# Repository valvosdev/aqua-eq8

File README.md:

# Aqua:eq8

> Open Hardware. Open Source. Smart Irrigation.

Aqua:eq8 is an open-source and open-hardware 8-zone smart irrigation controller designed for residential, commercial, greenhouse, and agricultural installations.

Built around the ESP32-C3-MINI-N4, Aqua:eq8 combines reliable irrigation control with secure connectivity, mobile management, OTA firmware updates, MQTT communication, and cloud integration while remaining fully self-hostable and hackable.

The project includes:

- ESP32 firmware
- Hardware schematics and PCB design
- Golang backend API
- React Native mobile application
- Docker, Kubernetes, and Helm deployment support

---

## Features

### Irrigation Control

- 8 independent irrigation zones
- Multiple zones can run simultaneously
- Configurable Master Valve support
- Configurable pump start delay
- Local manual operation without Internet
- Mobile application control
- MQTT-based communication
- Future scheduling support
- Future weather integration
- Emergency stop functionality

### Connectivity

- WiFi provisioning via BLE
- Bluetooth Low Energy onboarding
- MQTT communication
- OTA firmware updates
- Cloud synchronization
- Device telemetry

### Security

- ESP32 Secure Boot
- Flash Encryption
- Signed OTA updates
- TLS communication
- Device authentication
- Secure credential storage

### Reliability

- Offline-first operation
- Local control during Internet outages
- Hardware watchdog
- Software watchdog
- Automatic recovery
- Power-loss recovery

### Open Source

- Open firmware
- Open hardware
- Open API
- Open mobile app
- Self-hostable backend

---

# Repository Structure

```
aqua-eq8/
├── firmware/
│   ├── main/
│   ├── components/
│   ├── ble/
│   ├── wifi/
│   ├── mqtt/
│   ├── ota/
│   └── valve/
│
├── hardware/
│   ├── schematic/
│   ├── pcb/
│   ├── enclosure/
│   └── bom/
│
├── api/
│   ├── cmd/
│   ├── internal/
│   ├── deployments/
│   ├── helm/
│   └── docker/
│
├── mobile/
│   ├── src/
│   ├── ios/
│   └── android/
│
└── docs/

```

# Hardware

## Power

The controller is powered by a standard irrigation transformer.

### Input

text 24VAC Barrel Jack 

### Internal Rails

```
text 24VAC  ├── Valve Outputs  ├── Current Monitoring  └── AC/DC Converter       ├── 5V       └── 3.3V 
```
---

## Main Components

### MCU

- ESP32-C3-MINI-N4
- WiFi 2.4GHz
- Bluetooth Low Energy
- 4MB Flash

### Output Expansion

Two 74HC595 shift registers are used:

#### Shift Register #1

Controls:

- 8 TRIAC outputs
- 8 Green status LEDs

#### Shift Register #2

Controls:

- 8 Red Master LEDs

This minimizes GPIO usage while allowing future expansion.

### Valve Drivers

- TRIAC-based switching
- Designed for 24VAC sprinkler valves
- RC snubber protection per channel
- Future current sensing support

### Protection

- Input fuse
- Snubber protection on every channel
- Brownout protection
- Hardware watchdog
- Secure boot
- Flash encryption

---

# Channel Controls

## Channels 1-8

Each button controls one irrigation zone.

### Short Press

Toggle zone state.

| Current State | Action |
|--------------|----------|
| OFF | Turn ON |
| ON | Turn OFF |

### Long Press

Toggle Master Valve assignment.

| Current State | Action |
|--------------|----------|
| Normal Zone | Set as Master |
| Master Zone | Remove Master |

Only one channel may be configured as Master at a time.

---

# Master Valve Operation

A Master Valve is commonly used for:

- Main water supply
- Pump control
- Pressure system enable

When any non-master zone is enabled:

1. Master Valve turns ON immediately
2. Zone enters waiting state
3. Configurable delay timer starts
4. Zone activates after delay

Example:

text Channel 1 = Master  User enables Channel 3  Channel 1 ON immediately  Channel 3 LED flashes  5 second delay  Channel 3 ON 

When the last active zone stops:

text Channel 3 OFF  No active zones remaining  Channel 1 OFF 

### Default Delay

yaml master_delay_seconds: 5 

Configurable through the mobile application.

---

# Channel LED Behavior

Each channel button contains:

- Green LED
- Red LED

## Green LED

Indicates operational state.

| State | Green |
|---------|---------|
| OFF | OFF |
| Waiting Master Delay | Flashing |
| Active | Solid |

## Red LED

Indicates configuration state.

| State | Red |
|---------|---------|
| Normal Zone | OFF |
| Master Zone | Solid |

## Combined States

| State | Green | Red |
|---------|---------|---------|
| OFF | OFF | OFF |
| ON | ON | OFF |
| Master OFF | OFF | ON |
| Master ON | ON | ON |
| Waiting Delay | Flashing | OFF |

---

# Status Button (Button 9)

Button 9 is a dedicated RGB status and management button.

Functions:

- Device Status
- BLE Pairing
- Factory Reset

---

## RGB Status LED

The status LED always displays the highest priority state.

Priority:

text Error OTA Update BLE Connected BLE Advertising WiFi Connected Booting 

### States

| State | RGB |
|---------|---------|
| Booting | White Breathing |
| WiFi Connected | Solid Green |
| BLE Advertising | Blue Breathing |
| Mobile App Connected | Solid Blue |
| OTA Update | Purple Breathing |
| Error | Red Flashing |

---

## Button Actions

### Short Press

Enable BLE pairing mode.

LED:

text Blue Breathing 

Duration:

text 10 Minutes 

### Long Press (10 Seconds)

Factory Reset.

Deletes:

- WiFi Credentials
- MQTT Configuration
- Device Pairing
- Local Configuration
- Schedules

LED:

text Red Breathing 

Device automatically reboots.

---

# Connectivity

Aqua:eq8 intentionally avoids:

- Captive Portals
- Access Point Setup
- Embedded Web UI

All device provisioning is performed through Bluetooth Low Energy.

### Provisioning Flow

text Power Device       ↓ Press Status Button       ↓ BLE Pairing       ↓ Mobile App       ↓ Send WiFi Credentials       ↓ Connect to Network       ↓ Register with Backend       ↓ MQTT Connected 

---

# MQTT

MQTT is the primary communication mechanism between the controller and backend services.

## Topics

text aquaeq8/{deviceId}/state aquaeq8/{deviceId}/events aquaeq8/{deviceId}/telemetry aquaeq8/{deviceId}/command aquaeq8/{deviceId}/ota 

## Example Telemetry

json {   "uptime": 86400,   "wifi_rssi": -62,   "free_heap": 124832,   "active_zones": [2,4,7] } 

MQTT data can be consumed directly by:

- Telegraf
- InfluxDB
- TimescaleDB
- VictoriaMetrics
- Grafana

---

# Firmware

Location:

text /firmware 

Built using:

- ESP-IDF
- FreeRTOS
- C/C++

## Features

### Device Control

- Zone management
- Master Valve logic
- Delay handling
- Local operation

### Connectivity

- BLE provisioning
- WiFi management
- MQTT client

### OTA

- Signed firmware updates
- Rollback protection
- Secure update process

### Security

- Secure Boot
- Flash Encryption
- Device authentication

### Reliability

- Hardware watchdog
- Software watchdog
- Crash recovery

---

# Backend API

Location:

text /api 

Built using:

- Go 1.26+
- PostgreSQL
- Redis
- MQTT

## Features

### Device Management

- Device registration
- Pairing
- Configuration synchronization

### Monitoring

- Online/offline status
- Telemetry collection
- Device diagnostics

### Security

- JWT authentication
- TLS communication
- API rate limiting

---

# Deployment

## Docker

bash docker compose up -d 

## Kubernetes

bash kubectl apply -f deployments/ 

## Helm

bash helm install aquaeq8 ./helm 

---

# Mobile Application

Location:

text /mobile 

Built using:

- React Native
- TypeScript

## Features

### Device Setup

- BLE discovery
- WiFi provisioning
- Device pairing

### Device Management

- Zone control
- Master Valve configuration
- Delay configuration

### Monitoring

- Device health
- Connectivity status
- Telemetry visualization

### OTA

- Firmware update notifications
- Update progress monitoring

---

# Future Features

## Planned

- Irrigation schedules
- Weather integration
- Rain delay
- Seasonal adjustments
- Water usage analytics

## Hardware Expansion

- Flow meter support
- Rain sensor input
- Valve current monitoring
- Leak detection
- Pump monitoring

---

# Valve Current Monitoring

Future versions may include electrical current sensing on each output channel.

Benefits:

- Detect disconnected valves
- Detect broken wires
- Detect short circuits
- Detect stuck valves
- Improve diagnostics

Example:

text Zone 4 ON  Expected Current: 220mA Measured Current: 0mA  Alert: Valve Not Connected 

---

# Development

## [Firmware](firmware)

bash cd firmware  idf.py build idf.py flash idf.py monitor 

## [Backend](api)

bash cd api  go run ./cmd/server 

## [Mobile](mobile)

bash cd mobile  yarn install

bash cd mobile  yarn install yarn start 

---

# Security Model

Every controller includes:

- Unique Device ID
- Device Certificate
- Private Key

Firmware security:

- Secure Boot enabled
- Flash Encryption enabled
- Signed OTA updates only

The controller never accepts unsigned firmware images.

---

# Contributing

Contributions are welcome.

Areas where help is needed:

- Embedded development
- Hardware design
- Backend development
- Mobile development
- Testing
- Documentation

Please open an issue or submit a pull request.

---

# License

MIT License

See [LICENSE](LICENSE) for details.

---

# Philosophy

Aqua:eq8 is built around three principles.

## Open Source

All software is publicly available.

## Open Hardware

PCB layouts and schematics are publicly available.

## Local First

Your irrigation system continues operating even if the Internet does not.

---

Aqua:eq8

An open-source, secure, MQTT-native irrigation controller built for modern gardens, farms, and greenhouses.

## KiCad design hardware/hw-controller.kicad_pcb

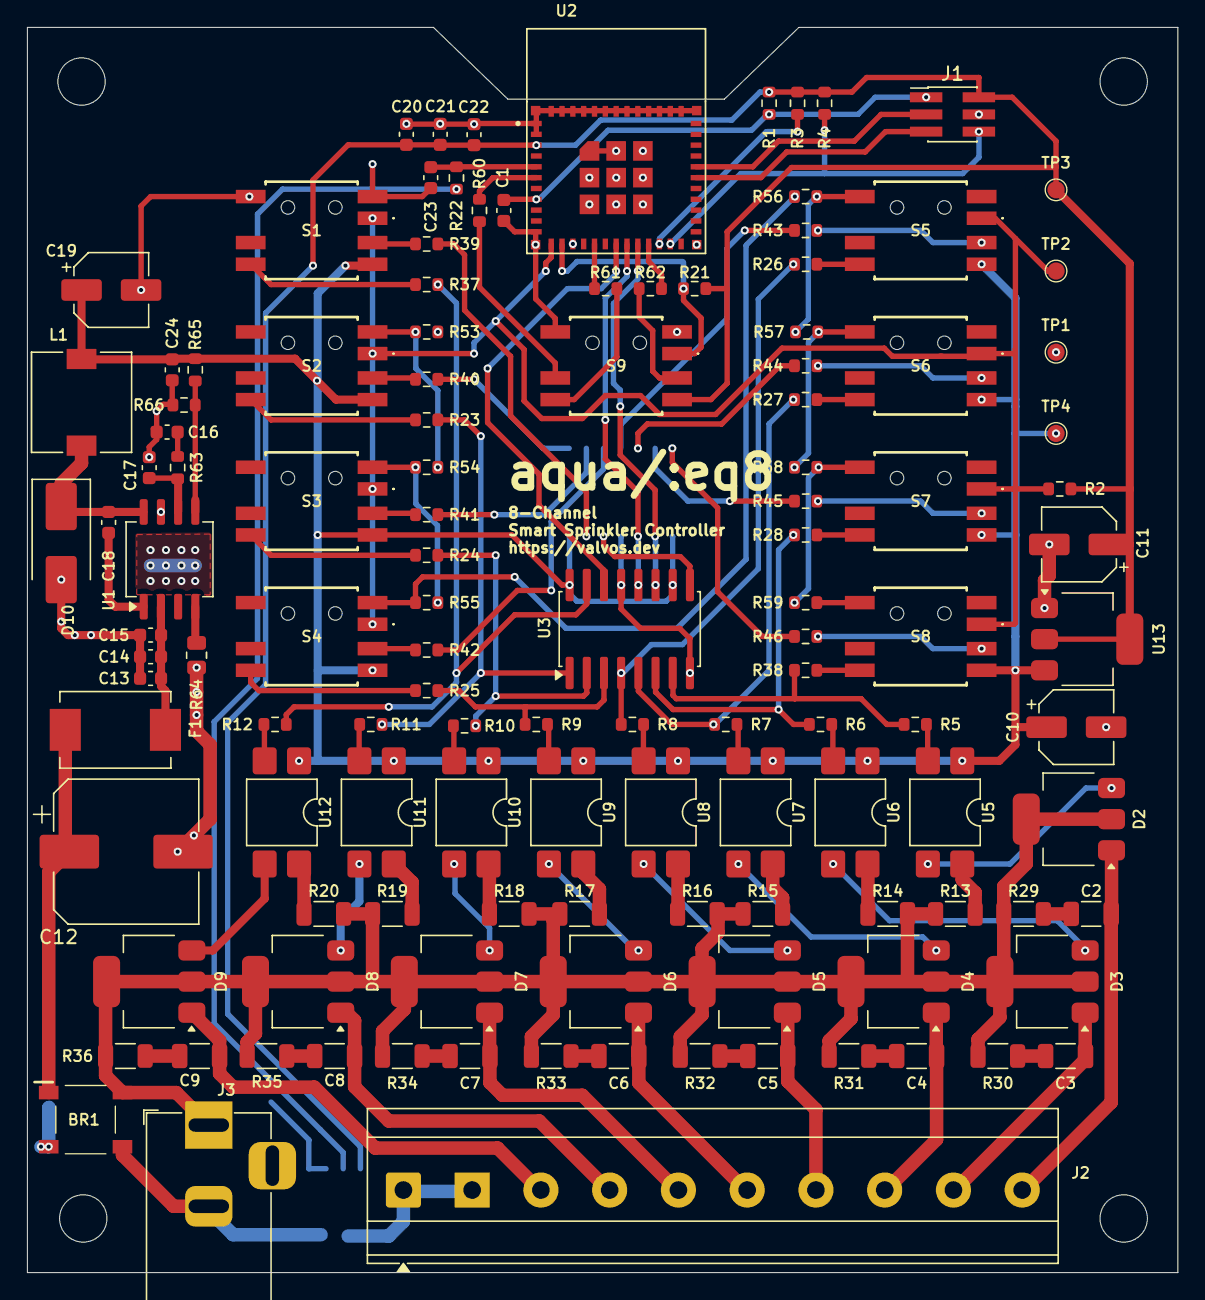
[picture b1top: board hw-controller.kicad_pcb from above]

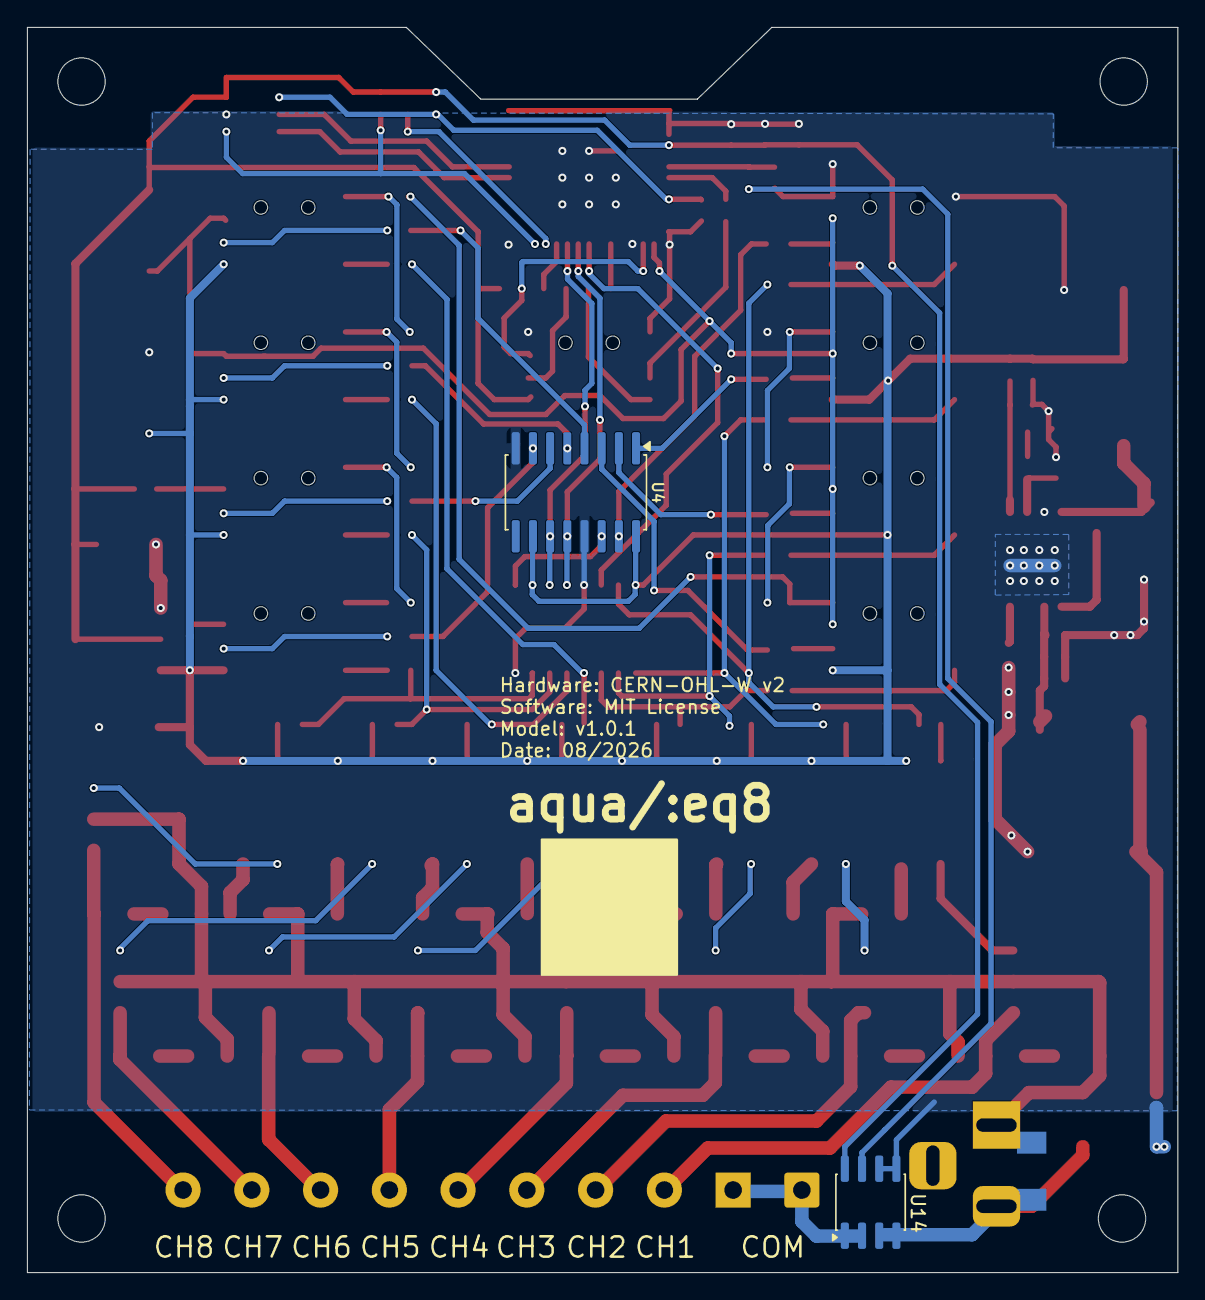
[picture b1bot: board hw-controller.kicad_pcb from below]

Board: 2 copper layers, 85.0 x 92.0 mm, 131 parts (3 on the bottom side), 112 nets.

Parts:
BR1: ABS10A-13; ABS10A13
C1, C22: 1uF; C_0603_1608Metric
C2, C3, C4, C5, C6, C7, C8, C9: 10nF; C_1206_3216Metric
C10, C11: 10uF; CP_Elec_5x5.7
C12: 47uF; CP_Elec_10x10.5
C13, C14: 2.2uF; C_0603_1608Metric
C15, C18, C21, C23: 0.1uF; C_0603_1608Metric
C16: 5.6nF; C_0603_1608Metric
C17: 12pF; C_0603_1608Metric
C19: 47uF; CP_Elec_5x5.7
C20: 10uF; C_0603_1608Metric
C24: 22uF; C_0603_1608Metric
D1: D_TVS_Small_Filled; DO-214AA
D2, D3, D4, D5, D6, D7, D8, D9: Z0103MN; SOT-223
D10: B360A-13-F; D_SMB_Handsoldering
F1: Fuse; Fuse_Bourns_MF-SM_7.98x5.44mm
H1, H2, H3, H4: MH; MountingHole_3.5mm
J1: Conn_02x03_Odd_Even; PinHeader_2x03_P1.27mm_Vertical_SMD
J2: Conn_01x10; TerminalBlock_Phoenix_MKDS-3-10-5.08_1x10_P5.08mm_Horizontal
J3: Jack-DC; BarrelJack_Horizontal
L1: 15uH; L_7.3x7.3_H4.5
R1, R2, R3, R4, R21, R66: 10k; R_0603_1608Metric
R5, R6, R7, R8, R9, R10, R11, R12, R23, R24, R25, R26, R27, R28, R37, R38, R39, R40, R41, R42, R43, R44, R45, R46: 470; R_0603_1608Metric
R13, R14, R15, R16, R17, R18, R19, R20: 330; R_1206_3216Metric
R22: 33; R_0603_1608Metric
R29, R30, R31, R32, R33, R34, R35, R36: 160; R_1206_3216Metric
R53, R54, R55, R56, R57, R58, R59: 1.8k; R_0603_1608Metric
R60, R61, R62: 150; R_0603_1608Metric
R63: 20k; R_0603_1608Metric
R64: 400k; R_0805_2012Metric
R65: 50k; R_0603_1608Metric
S1: RGBFR_CH1; 228EMVARGBFR
S2: RGBFR_CH2; 228EMVARGBFR
S3: RGBFR_CH3; 228EMVARGBFR
S4: RGBFR_CH4; 228EMVARGBFR
S5: RGBFR_CH5; 228EMVARGBFR
S6: RGBFR_CH6; 228EMVARGBFR
S7: RGBFR_CH7; 228EMVARGBFR
S8: RGBFR_CH8; 228EMVARGBFR
S9: RGBFR_STATUS; 228EMVARGBFR
TP1, TP2, TP3, TP4: TP_1_27
U1: RT6362GSP; SOIC-8_5.3x6.2mm_P1.27mm
U2: ESP32-C3-MINI-1-N4; XCVR_ESP32-C3-MINI-1-N4
U3, U4: 74HC595; SOIC-16W_5.3x10.2mm_P1.27mm
U5, U6, U7, U8, U9, U10, U11, U12: FODM3053; SMDIP-4_W7.62mm
U13: AMS1117-3.3; SOT-223-3_TabPin2
U14: ACS725xLCTR-20AB; SOIC-8_3.9x4.9mm_P1.27mm

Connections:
+3.3V: C11.1, C20.1, C21.1, C22.1, J1.2, R1.1, R2.1, R3.1, R4.1, R21.1, S9.L1 (COM_A), TP3.1 (TP_1), U2.3 (3V3), U13.2 (VO), U14.8 (VCC)
+5V: C10.1, C19.1, C24.1, L1.2, R65.2, S1.L1 (COM_A), S2.L1 (COM_A), S3.L1 (COM_A), S4.L1 (COM_A), S5.L1 (COM_A), S6.L1 (COM_A), S7.L1 (COM_A), S8.L1 (COM_A), TP4.1 (TP_1), U3.10 (~SRCLR), U3.16 (VCC), U4.10 (~SRCLR), U4.16 (VCC), U5.1, U6.1, U7.1, U8.1, U9.1, U10.1, U11.1, U12.1, U13.3 (VI)
/24VAC1: BR1.2 (~_1), D1.2 (A2), D2.2 (A2), D2.4 (A4), D3.2 (A2), D3.4 (A4), D4.2 (A2), D4.4 (A4), D5.2 (A2), D5.4 (A4), D6.2 (A2), D6.4 (A4), D7.2 (A2), D7.4 (A4), D8.2 (A2), D8.4 (A4), D9.2 (A2), D9.4 (A4), J3.1, R13.2, R14.2, R15.1, R16.2, R17.1, R18.2, R19.1, R20.2, R29.1, R30.1, R31.1, R32.1, R33.1, R34.1, R35.1, R36.1
/24VAC2: BR1.4 (~_2), D1.1 (A1), J3.2, U14.3 (IP-), U14.4 (IP-)
/24VAC2_OUT: J2.1, J2.2, U14.1 (IP+), U14.2 (IP+)
ACS_ADC: C23.1, R22.2, U2.5 (IO2)
BTNS_PIN: R2.2, S1.A1 (COM), S2.A1 (COM), S3.A1 (COM), S4.A1 (COM), S5.A1 (COM), S6.A1 (COM), S7.A1 (COM), S8.A1 (COM), TP2.1 (TP_1), U2.12 (IO0)
EN: C1.1, J1.1, R1.2, U2.8 (EN)
GND: BR1.3 (-), C1.2, C10.2, C11.2, C12.2, C13.2, C14.2, C15.2, C16.1, C17.1, C19.2, C20.2, C21.2, C22.2, C23.2, C24.2, D10.2 (A), J1.4, R53.2, R64.1, R66.1, S1.B1 (NO_1), S1.B2 (NO_2), S9.B1 (NO_1), S9.B2 (NO_2), TP1.1 (TP_1), U1.7 (GND), U2.1 (GND), U2.2 (GND), U2.11 (GND), U2.14 (GND), U2.36 (GND), U2.37 (GND), U2.38 (GND), U2.39 (GND), U2.40 (GND), U2.41 (GND), U2.42 (GND), U2.43 (GND), U2.44 (GND), U2.45 (GND), U2.46 (GND), U2.47 (GND), U2.48 (GND), U2.49_1 (GND), U2.49_2 (GND), U2.49_3 (GND), U2.49_4 (GND), U2.49_5 (GND), U2.49_6 (GND), U2.49_7 (GND), U2.49_8 (GND), U2.49_9 (GND), U2.50 (GND), U2.51 (GND), U2.52 (GND), U2.53 (GND), U3.8 (GND), U3.13 (~OE), U4.8 (GND), U4.13 (~OE), U13.1 (GND), U14.5 (GND), U14.6 (FILTER)
LATCH: U2.19 (IO5), U3.12 (RCLK), U4.12 (RCLK)
LEDG_CH1: R39.2, U4.15 (QA)
LEDG_CH2: R40.2, U4.1 (QB)
LEDG_CH3: R41.2, U4.2 (QC)
LEDG_CH4: R42.2, U4.3 (QD)
LEDG_CH5: R43.1, U4.4 (QE)
LEDG_CH6: R44.1, U4.5 (QF)
LEDG_CH7: R45.1, U4.6 (QG)
LEDG_CH8: R46.1, U4.7 (QH)
LEDR_CH1: R12.2, R37.2, U3.15 (QA)
LEDR_CH2: R11.2, R23.2, U3.1 (QB)
LEDR_CH3: R10.2, R24.2, U3.2 (QC)
LEDR_CH4: R9.1, R25.2, U3.3 (QD)
LEDR_CH5: R8.1, R26.1, U3.4 (QE)
LEDR_CH6: R7.1, R27.1, U3.5 (QF)
LEDR_CH7: R6.1, R28.1, U3.6 (QG)
LEDR_CH8: R5.1, R38.1, U3.7 (QH)
unnamed: BR1.1 (+), C12.1, F1.1
unnamed: C2.1, R29.2
unnamed: C3.1, R30.2
unnamed: C4.1, R31.2
unnamed: C5.1, R32.2
unnamed: C6.1, R33.2
unnamed: C7.1, R34.2
unnamed: C8.1, R35.2
unnamed: C9.1, R36.2
unnamed: C16.2, R63.1
unnamed: C2.2, D2.1 (A1), J2.10
unnamed: D2.3 (G), U5.3
unnamed: C3.2, D3.1 (A1), J2.9
unnamed: D3.3 (G), U6.3
unnamed: C4.2, D4.1 (A1), J2.8
unnamed: D4.3 (G), U7.3
unnamed: C5.2, D5.1 (A1), J2.7
unnamed: D5.3 (G), U8.3
unnamed: C6.2, D6.1 (A1), J2.6
unnamed: D6.3 (G), U9.3
unnamed: C7.2, D7.1 (A1), J2.5
unnamed: D7.3 (G), U10.3
unnamed: C8.2, D8.1 (A1), J2.4
unnamed: D8.3 (G), U11.3
unnamed: C9.2, D9.1 (A1), J2.3
unnamed: D9.3 (G), U12.3
unnamed: C18.2, D10.1 (K), L1.1, U1.8 (SW)
unnamed: R5.2, U5.2
unnamed: R6.2, U6.2
unnamed: R7.2, U7.2
unnamed: R8.2, U8.2
unnamed: R9.2, U9.2
unnamed: R10.1, U10.2
unnamed: R11.1, U11.2
unnamed: R12.1, U12.2
unnamed: R13.1, U5.4
unnamed: R14.1, U6.4
unnamed: R15.2, U7.4
unnamed: R16.1, U8.4
unnamed: R17.2, U9.4
unnamed: R18.1, U10.4
unnamed: R19.2, U11.4
unnamed: R20.1, U12.4
unnamed: R39.1, S1.L2 (K_GREEN)
unnamed: R37.1, S1.L3 (K_RED)
unnamed: R40.1, S2.L2 (K_GREEN)
unnamed: R23.1, S2.L3 (K_RED)
unnamed: R53.1, R54.2, S2.B1 (NO_1), S2.B2 (NO_2)
unnamed: R41.1, S3.L2 (K_GREEN)
unnamed: R24.1, S3.L3 (K_RED)
unnamed: R54.1, R55.2, S3.B1 (NO_1), S3.B2 (NO_2)
unnamed: R42.1, S4.L2 (K_GREEN)
unnamed: R25.1, S4.L3 (K_RED)
unnamed: R55.1, R56.1, S4.B1 (NO_1), S4.B2 (NO_2)
unnamed: R43.2, S5.L2 (K_GREEN)
unnamed: R26.2, S5.L3 (K_RED)
unnamed: R56.2, R57.1, S5.B1 (NO_1), S5.B2 (NO_2)
unnamed: R44.2, S6.L2 (K_GREEN)
unnamed: R27.2, S6.L3 (K_RED)
unnamed: R57.2, R58.1, S6.B1 (NO_1), S6.B2 (NO_2)
unnamed: R45.2, S7.L2 (K_GREEN)
unnamed: R28.2, S7.L3 (K_RED)
unnamed: R58.2, R59.1, S7.B1 (NO_1), S7.B2 (NO_2)
unnamed: R46.2, S8.L2 (K_GREEN)
unnamed: R38.2, S8.L3 (K_RED)
unnamed: R59.2, S8.B1 (NO_1), S8.B2 (NO_2)
unnamed: R60.2, S9.L4 (K_BLUE)
unnamed: R62.2, S9.L2 (K_GREEN)
unnamed: R61.2, S9.L3 (K_RED)
unnamed: C18.1, U1.1 (BOOT)
unnamed: C17.2, R63.2, U1.6 (COMP)
unnamed: R65.1, R66.2, U1.5 (FB)
unnamed: R64.2, U1.4 (RT/SYNC)
unnamed: C13.1, C14.1, C15.1, F1.2, U1.2 (VIN)
unnamed: U3.9 (QH'), U4.14 (SER)
unnamed: R22.1, U14.7 (VIOUT)
RX: J1.5, U2.30 (RXD0)
SCL: J1.6, R4.2, U2.23 (IO9)
SDA: R3.2, U2.22 (IO8)
SIPO_DATA: U2.18 (IO4), U3.14 (SER)
SIPO_SCK: U2.20 (IO6), U3.11 (SRCLK), U4.11 (SRCLK)
STATUS_BTN_PIN: R21.2, S9.A1 (COM), U2.13 (IO1)
STATUS_LEDB_PIN: R60.1, U2.6 (IO3)
STATUS_LEDG_PIN: R62.1, U2.21 (IO7)
STATUS_LEDR_PIN: R61.1, U2.16 (IO10)
TX: J1.3, U2.31 (TXD0)

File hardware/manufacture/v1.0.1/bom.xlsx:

Id | Designator | Footprint | Quantity | Designation
1 | BR1 | ABS10A13 | 1 | ABS10A-13
2 | C1, C22 | C_0603_1608Metric | 2 | 1uF
3 | C2, C3, C4, C5, C6, C7, C8, C9 | C_1206_3216Metric | 8 | 10nF
4 | C10, C11 | CP_Elec_5x5.7 | 2 | 10uF
5 | C12 | CP_Elec_10x10.5 | 1 | 47uF
6 | C13, C14 | C_0603_1608Metric | 2 | 2.2uF
7 | C15, C18, C21, C23 | C_0603_1608Metric | 4 | 0.1uF
8 | C16 | C_0603_1608Metric | 1 | 5.6nF
9 | C17 | C_0603_1608Metric | 1 | 12pF
10 | C19 | CP_Elec_5x5.7 | 1 | 47uF
11 | C20 | C_0603_1608Metric | 1 | 10uF
12 | C24 | C_0603_1608Metric | 1 | 22uF
13 | D1 | DO-214AA | 1 | D_TVS_Small_Filled
14 | D2, D3, D4, D5, D6, D7, D8, D9 | SOT-223 | 8 | Z0103MN
15 | D10 | D_SMB_Handsoldering | 1 | B360A-13-F
16 | F1 | Fuse_Bourns_MF-SM_7.98x5.44mm | 1 | Fuse
17 | J1 | PinHeader_2x03_P1.27mm_Vertical_SMD | 1 | Conn_02x03_Odd_Even
18 | J2 | TerminalBlock_Phoenix_MKDS-3-10-5.08_1x10_P5.08mm_Horizontal | 1 | Conn_01x10
19 | J3 | BarrelJack_Horizontal | 1 | Jack-DC
20 | L1 | L_7.3x7.3_H4.5 | 1 | 15uH
21 | R1, R2, R3, R4, R21, R66 | R_0603_1608Metric | 6 | 10k
22 | R5, R6, R7, R8, R9, R10, R11, R12, R23, R24, R25, R26, R27, R28, R37, R38, R39,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 | R_0603_1608Metric | 24 | 470
23 | R13, R14, R15, R16, R17, R18, R19, R20 | R_1206_3216Metric | 8 | 330
24 | R22 | R_0603_1608Metric | 1 | 33
25 | R29, R30, R31, R32, R33, R34, R35, R36 | R_1206_3216Metric | 8 | 160
26 | R53, R54, R55, R56, R57, R58, R59 | R_0603_1608Metric | 7 | 1.8k
27 | R60, R61, R62 | R_0603_1608Metric | 3 | 150
28 | R63 | R_0603_1608Metric | 1 | 20k
29 | R64 | R_0805_2012Metric | 1 | 400k
30 | R65 | R_0603_1608Metric | 1 | 50k
31 | S1-S9 | 228EMVARGBFR | 9 | RGBFR_CH1_8_Status
41 | U1 | SOIC-8_5.3x6.2mm_P1.27mm | 1 | RT6362GSP
42 | U2 | XCVR_ESP32-C3-MINI-1-N4 | 1 | ESP32-C3-MINI-1-N4
43 | U3, U4 | SOIC-16W_5.3x10.2mm_P1.27mm | 2 | 74HC595
44 | U5, U6, U7, U8, U9, U10, U11, U12 | SMDIP-4_W7.62mm | 8 | FODM3053
45 | U13 | SOT-223-3_TabPin2 | 1 | AMS1117-3.3
46 | U14 | SOIC-8_3.9x4.9mm_P1.27mm | 1 | ACS725xLCTR-20AB

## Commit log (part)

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2026-06-06 added first api project structure and api/http handler, Repository pattern, config. uber/fx used as Dependency Injection
2026-06-16 firmware first commit inplemented: 1. manually control each channel sqitch on/off 2. master set, working 3. wifi provisioning via ble sec2, hard witten salt and verifier
2026-06-18 refactored teh pcb , fixed: C12 - made TH Added ACS725 to read currect Replaced triacs with something smaller Z0103 IMPORTANT: esp pins been changed, not compatible with v1.0.0
2026-06-18 save changes
2026-06-24 added support for mqtt, added delay when there is a master
2026-06-24 fixed the master set and unset, on master set/unset display a visual feedback. encrised mqtt time to retry the connection
2026-06-24 added schedule manager/support
2026-06-25 changed some resistors and caps to 0603
2026-06-26 retrace, fixrule checker error
2026-06-26 generated bom, tried to unify components
2026-06-26 added mqtt support, no certs configured yet
2026-06-26 added certs and use them to communicate via a secure line
2026-06-28 added mqtt working support

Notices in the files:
hardware/hw-controller.kicad_pcb:
Hardware: CERN-OHL-W v2
Software: MIT License
